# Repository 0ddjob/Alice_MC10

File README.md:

# Purpose
Simple designs for the Tandy TRS-80 MC-10 and Matra Alice.

## [Internal 4KB-to-8KB RAM Upgrade](/Internal_8KB_RAM)
Upgrade the Alice or MC-10 internal RAM from 4KB to 8KB.  Note that the extra 4KB isn't available if the 16KB expansion is also attached.<br>

## [RGB Video Modification](/RGB_Video) (Work In Progress)
Convert the MC-10 video output from RF modulated to RGB - design is based on the Matra Alice.<br>

## [Expander](https://github.com/Fred72z/ALICE)
Check out [Fred72z's](https://github.com/Fred72z) excellent expansion for Alice & MC10 ... RAM, joysticks, cartridge.

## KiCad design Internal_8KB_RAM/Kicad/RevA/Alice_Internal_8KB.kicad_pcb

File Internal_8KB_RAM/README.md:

# Internal 4KB-to-8KB RAM Upgrade
## Background
This design is based on the work that Daniel Tufvesson documented on his [blog](https://www.waveguide.se/?article=expanding-the-trs-80-mc-10-internal-ram) for the Tandy TRS-80 MC-10. Please refer to his blog for the background and theory of the upgrade.<br>

Note that the additional 4KB is not usable with the 16KB RAM expansion as the expansion occupies the same space in memory.<br>

I have [tested Rev. A on my Alice](https://youtu.be/OvdkhOnV7no) but not yet (as of 27-Feb-2025) on my MC-10.<br>

## Why Do this?
The Alice/MC-10 shares its internal 4KB of RAM with the 6847 VDG.  The VDG can address up to 8KB of RAM but doesn't have access to the expansion bus, thus it can only access RAM that is installed internally.  The additional RAM allows access to additional video modes such as 128x192x4 and 256x192x2 graphics modes which require 6KB of RAM. <br>

Of course, software needs to be written to take advantage of this.<br>

## Free Memory
Standard Alice 4KB: 3142 bytes free<br>
Alice with 8KB: 7238 bytes free<br>
Standard Alice 4+16KB: 19526 bytes free<br>
Alice with 8+16KB: 19526 bytes free (additional 4KB overlapped)<br>

## Design
The MC-10 has a limitation with component height due to its rather [snug FCC shielding](https://www.waveguide.se/?article=getting-to-know-the-trs-80-mc-10) - the Matra Alice doesn't have this, hence this simple daughterboard design.  My MC-10 no longer has that limitation either!<br>

The Alice also doesn't have the bodge wiring for the 4KB address decoding that the MC-10 has.<br>

This is what the 8KB daughterboard looks like installed in the Alice:<br>

(Sidenote 1: yes, the crossing of the black and yellow 6847 VDG address wires annoys me too - I have since updated the PCB so they don't cross!)<br>

(Sidenote 2: the original Thomson 6803 CPU in my Alice was faulty causing [keyboard issues](https://youtu.be/A9SVZOl3z24) - I replaced it with a socketed Motorola 6803 seen on the left).<br>

On the MC-10 it is necessary to also move a bodge wire from A12 (6803 pin 25) to A13 (6803 pin 24).  On the Alice this simply requires cutting a track to pin 25 and connecting it to pin 24:<br>

## Bill Of Materials
- PCB (thanks to [PCBWay](www.pcbway.com) for their ongoing sponsorship)
- 6264 static RAM (I didn't bother with a socket to keep height to a minimum)
- 1KΩ resistor
- 3-pin right-angle header & 3-way Dupont-type wire (or just wire directly)
- two 12-pin headers (or single row cut into 12-pins)

For the 12-pin headers I normally use "turned" pins in case I'm installing into an IC socket.  In this case I've just installed directly onto the board so the more common square-shaped header pins could be used instead.

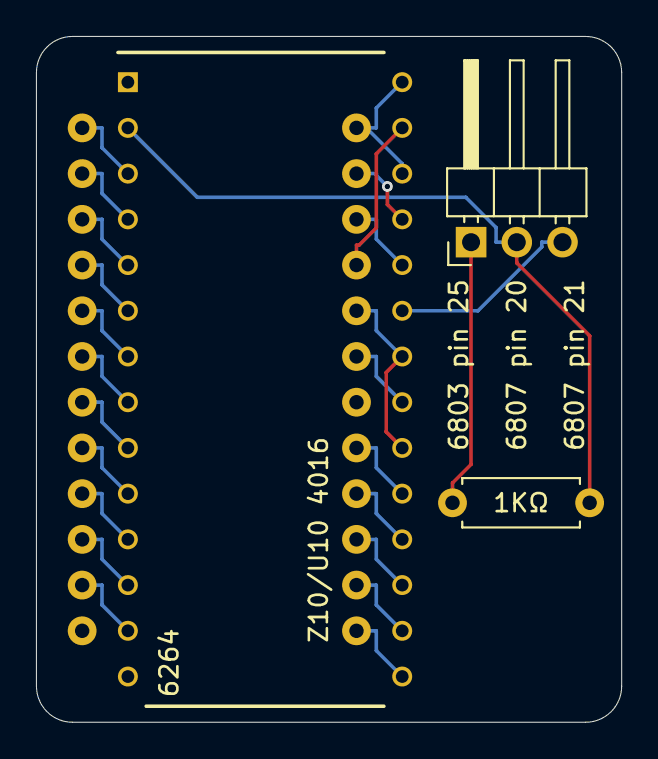
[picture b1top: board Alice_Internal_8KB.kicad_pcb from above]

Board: 2 copper layers, 32.5 x 38.1 mm, 4 parts (0 on the bottom side), 26 nets.

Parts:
J1: Conn_01x03; PinHeader_1x03_P2.54mm_Horizontal
R1: 1KΩ; R_Axial_DIN0207_L6.3mm_D2.5mm_P7.62mm_Horizontal
U1: 6264; DIP1524W51P254L3632H394Q28N
Z10: D4016; DIP-24_W15.24mm-Notch

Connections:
A0: U1.10 (A0), Z10.8
A1: U1.9 (A1), Z10.7
A2: U1.8 (A2), Z10.6
A3: U1.7 (A3), Z10.5
A4: U1.6 (A4), Z10.4
A5: U1.5 (A5), Z10.3
A6: U1.4 (A6), Z10.2
A7: U1.3 (A7), Z10.1
A8: U1.25 (A8), Z10.23
A9: U1.24 (A9), Z10.22
A10: U1.21 (A10), Z10.19
A11: J1.3 (6847_p20), U1.23 (A11)
A12: J1.2 (6847_p21), R1.1, U1.2 (A12)
D0: U1.11 (D0), Z10.9
D1: U1.12 (D1), Z10.10
D2: U1.13 (D2), Z10.11
D3: U1.15 (D3), Z10.13
D4: U1.16 (D4), Z10.14
D5: U1.17 (D5), Z10.15
D6: U1.18 (D6), Z10.16
D7: U1.19 (D7), Z10.17
GND: U1.14 (GND), Z10.12
unnamed: J1.1 (6803_p25), R1.2
Vcc: U1.26 (CE2), U1.28 (VCC), Z10.24
~OE: U1.20 (~CE1), U1.22 (~OE), Z10.20
~WE: U1.27 (~WR), Z10.21

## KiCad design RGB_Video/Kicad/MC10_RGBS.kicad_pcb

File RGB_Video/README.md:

# RGB Video Modification
## Background
This design is based on the Matra Alice schematic.  The Alice outputs an RGB+Audio signal via a 7-pin DIN socket - this would normally be connected to a Peritel or SCART connector.<br>

## Design Notes
### Transistor Replacements
The original design uses obsolete transistors: BC172C (NPN) and BC252C (PNP).  I've tried to match with available transistors - not an expert, happy to be advised of better matches:<br>
BC172C -> BC550C<br>
BC252C -> BC559C<br>

### Video Pinout (7-pin DIN)
The video pinout is:<br>
- Pin 1 = Vcc (+12V) - only needed for SCART switching? 
- Pin 2 = ground
- Pin 3 = red
- Pin 4 = synch
- Pin 5 = green
- Pin 6 = audio
- Pin 7 = blue

The +12V connection to the DIN can be connected via solder bridge (default open).<br>

### Input Signals Required
- SYS_CLK_IN = U12 pin 12 (74LS14)
- SYS_CLK_OUT = U12 pin 13
- ΦA = U11 pin 11 (MC6847 VDG)
- ΦB = U11 pin 10 (MC6847 VDG)
- CHB = U11 pin 9 (MC6847 VDG)
- Y = U11 pin 28 (MC6847 VDG)

### Notable Differences Between Alice & MC-10
The crystal for the Alice is located next to the 6803 CPU whereas the MC-10's crystal is part of the RF modulator circuit, being generated by the MC1372.  This means that any modification to the MC-10's video output stage needs to include the crystal & system clock generation circuitry.<br>

At the moment I have the crystal & MC1372 being recovered and re-used.<br>

## Status
16-Mar-2025:<br>
Work in progress!<br>
The schematic is almost complete, verifying against the Alice schematic (a bit hard to see some parts) and an actual Alice.<br>
A PCB will then be designed and test PCBs fabricated.

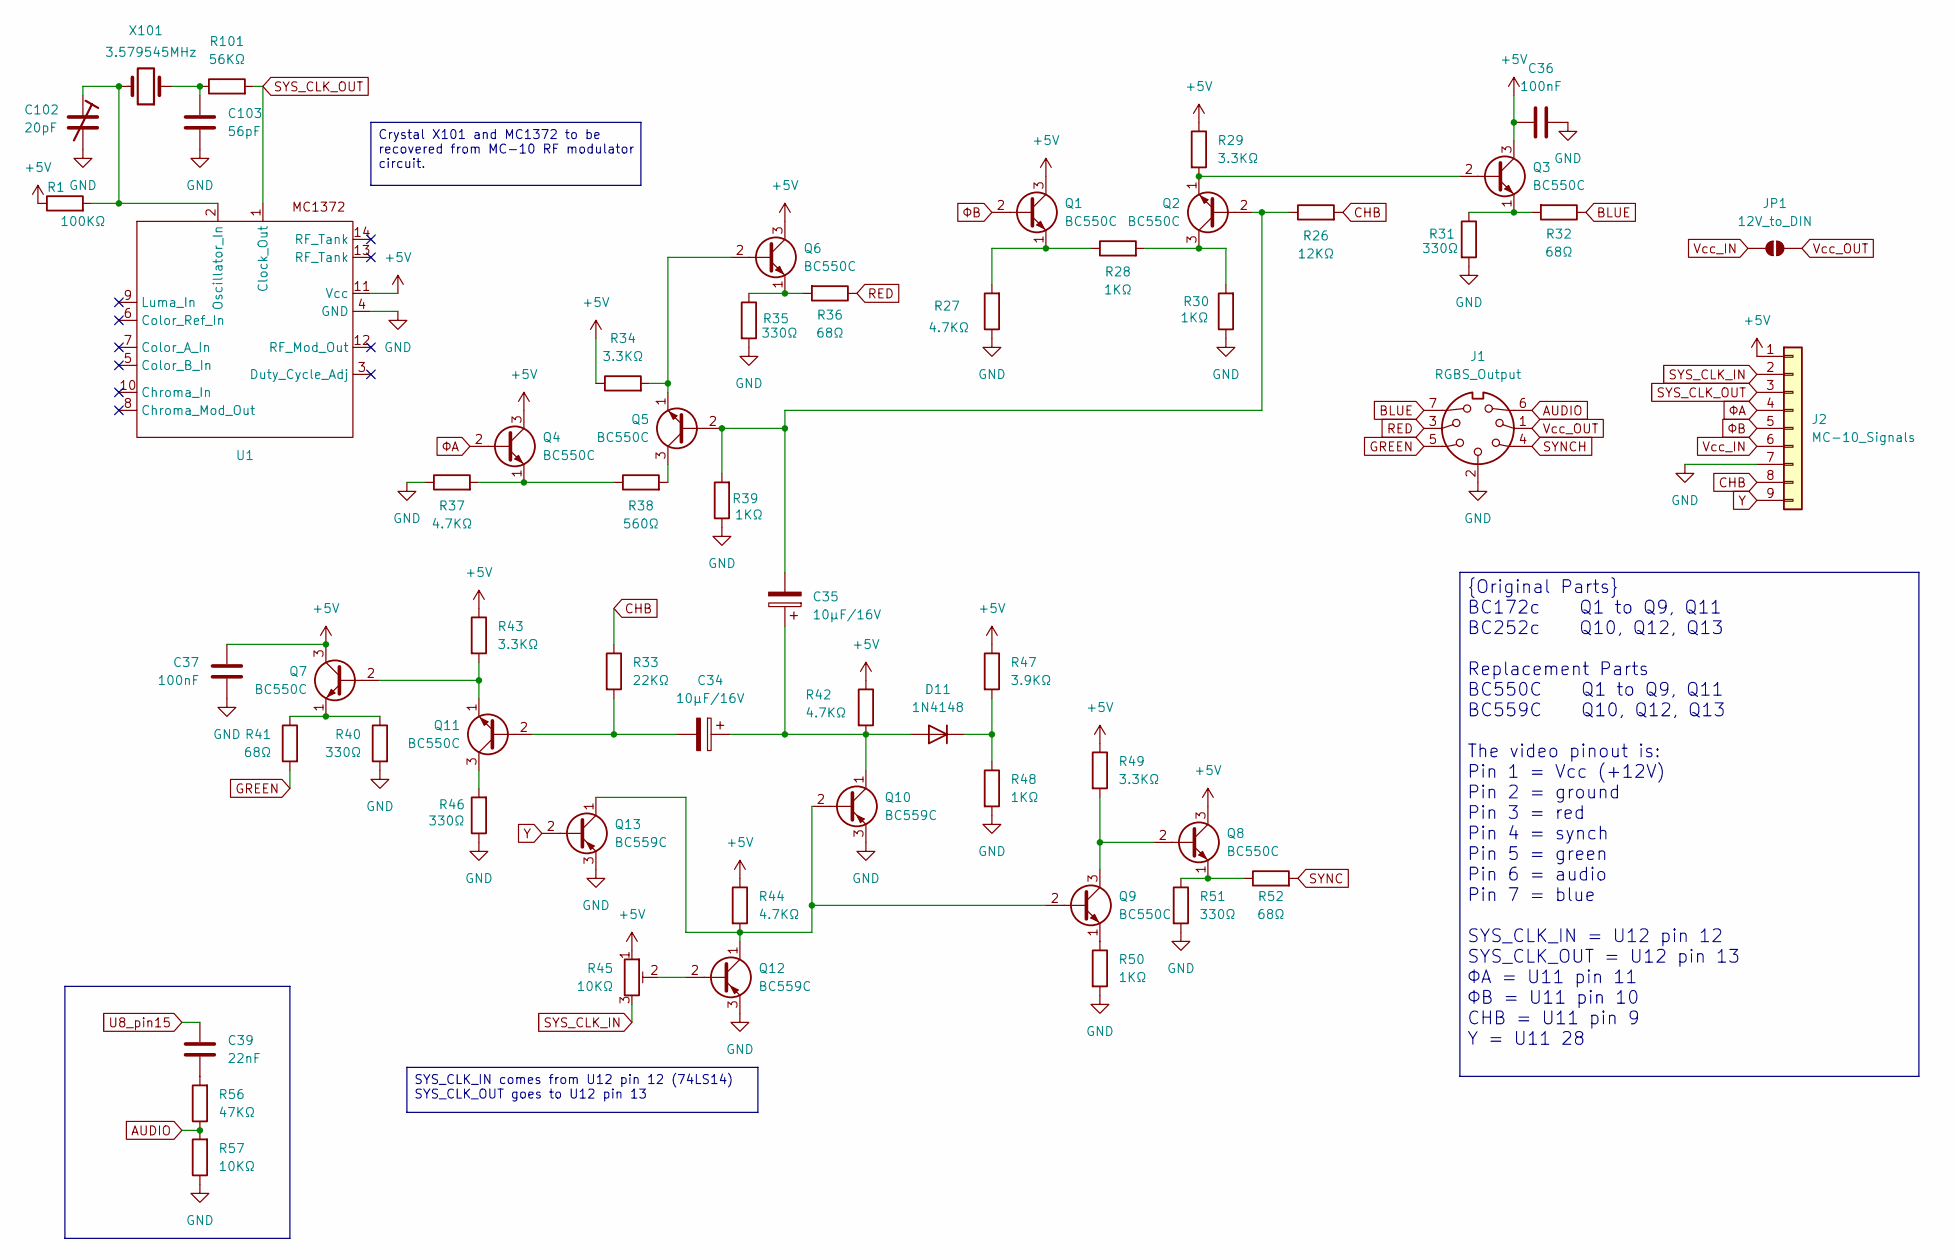
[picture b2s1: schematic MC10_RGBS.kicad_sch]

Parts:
C34, C35: 10µF/16V; CP_Radial_D5.0mm_P2.50mm
C36, C37: 100nF; C_Disc_D3.0mm_W2.0mm_P2.50mm
C39: 22nF; C_Disc_D3.0mm_W2.0mm_P2.50mm
C102: 20pF; C_Trimmer_Murata_TZB4-B
C103: 56pF; C_Disc_D3.0mm_W2.0mm_P2.50mm
D11: 1N4148; D_SOD-323_HandSoldering
J1: RGBS_Output; PinHeader_1x07_P2.54mm_Vertical
J2: MC-10_Signals; PinSocket_1x09_P2.54mm_Vertical
JP1: 12V_to_DIN; SolderJumper-2_P1.3mm_Open_Pad1.0x1.5mm
Q1, Q2, Q3, Q4, Q5, Q6, Q7, Q8, Q9, Q11: BC550C; TO-92_Inline
Q10, Q12, Q13: BC559C; TO-92_Inline
R1: 100KΩ; R_0603_1608Metric_Pad0.98x0.95mm_HandSolder
R26: 12KΩ; R_0603_1608Metric_Pad0.98x0.95mm_HandSolder
R27, R37, R42, R44: 4.7KΩ; R_0603_1608Metric_Pad0.98x0.95mm_HandSolder
R28, R30, R39, R48, R50: 1KΩ; R_0603_1608Metric_Pad0.98x0.95mm_HandSolder
R29, R34, R43, R49: 3.3KΩ; R_0603_1608Metric_Pad0.98x0.95mm_HandSolder
R31, R35, R40, R46, R51: 330Ω; R_0603_1608Metric_Pad0.98x0.95mm_HandSolder
R32, R36, R41, R52: 68Ω; R_0603_1608Metric_Pad0.98x0.95mm_HandSolder
R33: 22KΩ; R_0603_1608Metric_Pad0.98x0.95mm_HandSolder
R38: 560Ω; R_0603_1608Metric_Pad0.98x0.95mm_HandSolder
R45: 10KΩ; PTN091V10115K1B
R47: 3.9KΩ; R_0603_1608Metric_Pad0.98x0.95mm_HandSolder
R56: 47KΩ; R_0603_1608Metric_Pad0.98x0.95mm_HandSolder
R57: 10KΩ; R_0603_1608Metric_Pad0.98x0.95mm_HandSolder
R101: 56KΩ; R_0603_1608Metric_Pad0.98x0.95mm_HandSolder
U1: DIP-14_W7.62mm
X101: 3.579545MHz; Crystal_HC49-U_Vertical

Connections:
+5V: C36.1, C37.1, J2.1, Q1.3 (C), Q3.3 (C), Q4.3 (C), Q6.3 (C), Q7.3 (C), Q8.3 (C), R1.1, R29.1, R34.1, R42.1, R43.1, R44.1, R45.1, R47.1, R49.1, U1.11 (Vcc)
AUDIO: J1.6, R56.1, R57.2
BLUE: J1.7, R32.1
CHB: J2.8, R26.2, R33.1
GND: C36.2, C37.2, C102.2, C103.2, J1.2, J2.7, Q10.3 (E), Q12.3 (E), Q13.3 (E), R27.1, R30.1, R31.2, R35.2, R37.1, R39.1, R40.2, R46.1, R48.2, R50.2, R51.2, R57.1, U1.4 (GND)
GREEN: J1.5, R41.2
unnamed: C39.1, R56.2
unnamed: C103.1, R101.1, X101.1
unnamed: C34.1, C35.1, D11.2 (A), Q10.1 (C), R42.2
unnamed: D11.1 (K), R47.2, R48.1
unnamed: Q1.1 (E), R27.2, R28.1
unnamed: C35.2, Q2.2 (B), Q5.2 (B), R26.1, R39.2
unnamed: Q2.3 (C), R28.2, R30.2
unnamed: Q2.1 (E), Q3.2 (B), R29.2
unnamed: Q3.1 (E), R31.1, R32.2
unnamed: Q4.1 (E), R37.2, R38.1
unnamed: Q5.3 (C), R38.2
unnamed: Q5.1 (E), Q6.2 (B), R34.2
unnamed: Q6.1 (E), R35.1, R36.2
unnamed: Q7.1 (E), R40.1, R41.1
unnamed: Q8.2 (B), Q9.3 (C), R49.2
unnamed: Q8.1 (E), R51.1, R52.1
unnamed: Q9.1 (E), R50.1
unnamed: Q9.2 (B), Q10.2 (B), Q12.1 (C), Q13.1 (C), R44.2
unnamed: C34.2, Q11.2 (B), R33.2
unnamed: Q11.3 (C), R46.2
unnamed: Q7.2 (B), Q11.1 (E), R43.2
unnamed: Q12.2 (B), R45.2
unnamed: C102.1, R1.2, U1.2 (Oscillator_In), X101.2
RED: J1.3, R36.1
SYNC: R52.2
SYNCH: J1.4
SYS_CLK_IN: J2.2, R45.3
SYS_CLK_OUT: J2.3, R101.2, U1.1 (Clock_Out)
U8_pin15: C39.2
Vcc_IN: J2.6, JP1.1 (A)
Vcc_OUT: J1.1, JP1.2 (B)
Y: J2.9, Q13.2 (B)
ΦA: J2.4, Q4.2 (B)
ΦB: J2.5, Q1.2 (B)

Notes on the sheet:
{Original Parts} BC172c Q1 to Q9, Q11 BC252c Q10, Q12, Q13 Replacement Parts BC550C Q1 to Q9, Q11 BC559C Q10, Q12, Q13 The video pinout is: Pin 1 = Vcc (+12V) Pin 2 = ground Pin 3 = red Pin 4 = synch Pin 5 = green Pin 6 = audio Pin 7 = blue SYS_CLK_IN = U12 pin 12 SYS_CLK_OUT = U12 pin 13 ΦA = U11 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
SYS_CLK_IN comes from U12 pin 12 (74LS14) SYS_CLK_OUT goes to U12 pin 13
Crystal X101 and MC1372 to be recovered from MC-10 RF modulator circuit.

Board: 2 copper layers, 57 parts (0 on the bottom side), 37 nets, no tracks yet.

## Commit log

2025-02-26 spaces-to-underscore in filenames
2025-02-26 Free memory with 8KB upgrade
2025-02-26 Add schematic & VDG mode info
2025-02-27 Rearrange files
2025-02-27 Additional images
2025-03-14 Added RGB video section
2025-03-14 Formatting updates
2025-03-14 Renamed schematic
2025-03-14 Added images of Alice RGB output stage
2025-03-16 Added MC1372 for system clock generation
2025-03-16 Added MC1372 datasheet
2025-04-28 Changed transistor types
2025-04-28 Updated design with Rev. B
